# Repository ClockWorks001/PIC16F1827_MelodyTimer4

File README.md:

# PIC16F1827 Melody Timer Project.
---
This is a simple kitchen/cooking timer by [PIC16F1827][1].
It can choose which of 3 minutes, 5 minutes and 10 minutes.

## Description

This is a simple kitchen/cooking timer by [PIC16F1827][1].
It can choose which of 3 minutes, 5 minutes and 10 minutes.
When it became end of time, it sounds a melody.

I use following peripherals for this Melody Timer project.
  *TMR1* (with interrupt. It makes 1mil second interval.)
  *TMR2*
  *ECCP2*(with TMR2. I use it for PWM output. It buzz a piezo sounder.)
  *GPIO*(input x2 for Switches, output x3 for LED1, LED2, LED3)

Other references.
  <https://docs.google.com/spreadsheets/d/1fajrvUh0QQHbjQNBCf9UKNRYu8I2-zE32fsanEHT9bc/edit?usp=sharing>

## Demo

## Prerequisites

I created this project using the free versions of the following tools:
 * [Microchip MPLAB X][2] (v2.3)
 * [Microchip XC8 Compiler][3] (v1.32)
 * [MPLAB Code Configurator][4] (installed as plugin within MPLAB X)
 * [KICAD][6] (BZR4022)

You will need to download and install these tools appropriately before you
can open this project and build it.
I use the [Microchip MPLAB PICkit3 In-Circuit Debugger][5] to program
the chip and debug it.  

## Licence

[MIT](https://github.com/tcnksm/tool/blob/master/LICENCE)

## Author

Hiroshi Murakami  
<https://github.com/ClockWorks001>  

[1]: http://www.microchip.com/wwwproducts/Devices.aspx?dDocName=en538963 "PIC16F1827"
[2]: http://www.microchip.com/pagehandler/en-us/family/mplabx/ "MPLAB X"
[3]: http://www.microchip.com/pagehandler/en_us/devtools/mplabxc/ "MPLAB XC Compilers"
[4]: http://www.microchip.com/pagehandler/en-us/press-release/microchips-free-code-configura.html "MPLAB Code Configurator"
[5]: http://www.microchip.com/Developmenttools/ProductDetails.aspx?PartNO=PG164130 "MPLAB PICkit3 In-Circuit Debugger"
[6]: http://www.kicad-pcb.org/display/KICAD/KiCad+EDA+Software+Suite "KICAD"

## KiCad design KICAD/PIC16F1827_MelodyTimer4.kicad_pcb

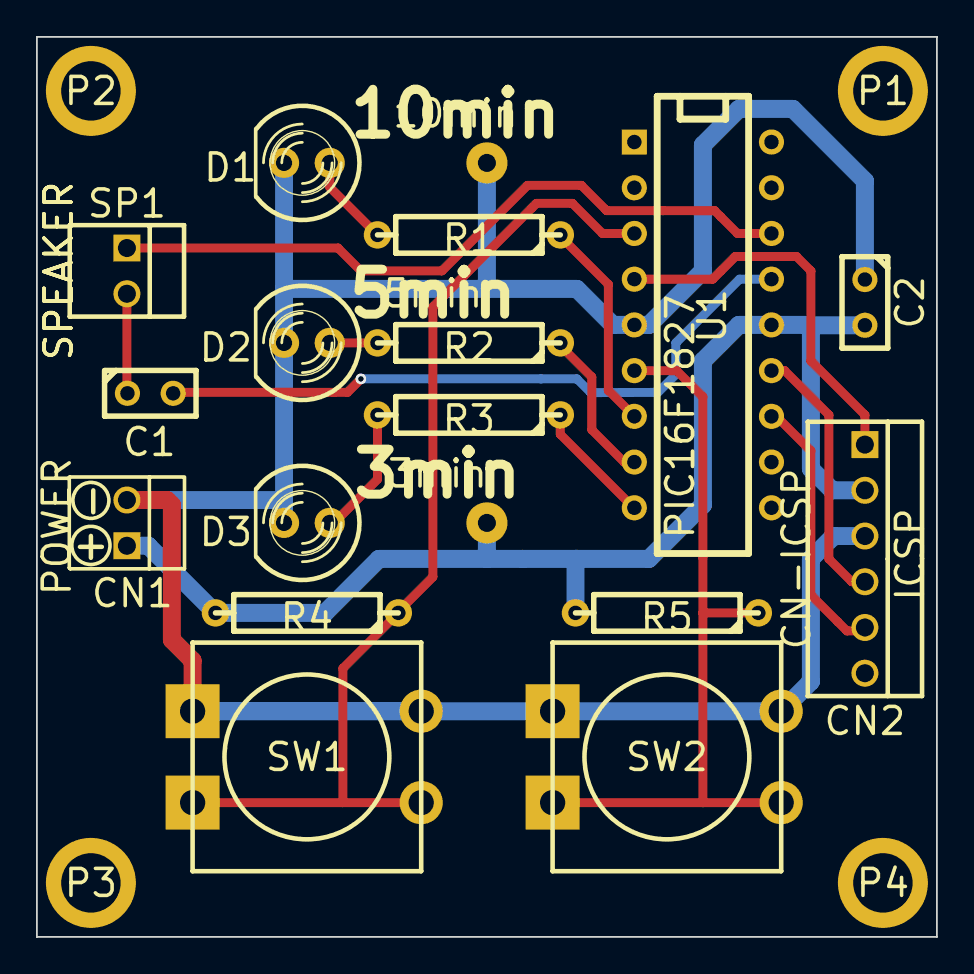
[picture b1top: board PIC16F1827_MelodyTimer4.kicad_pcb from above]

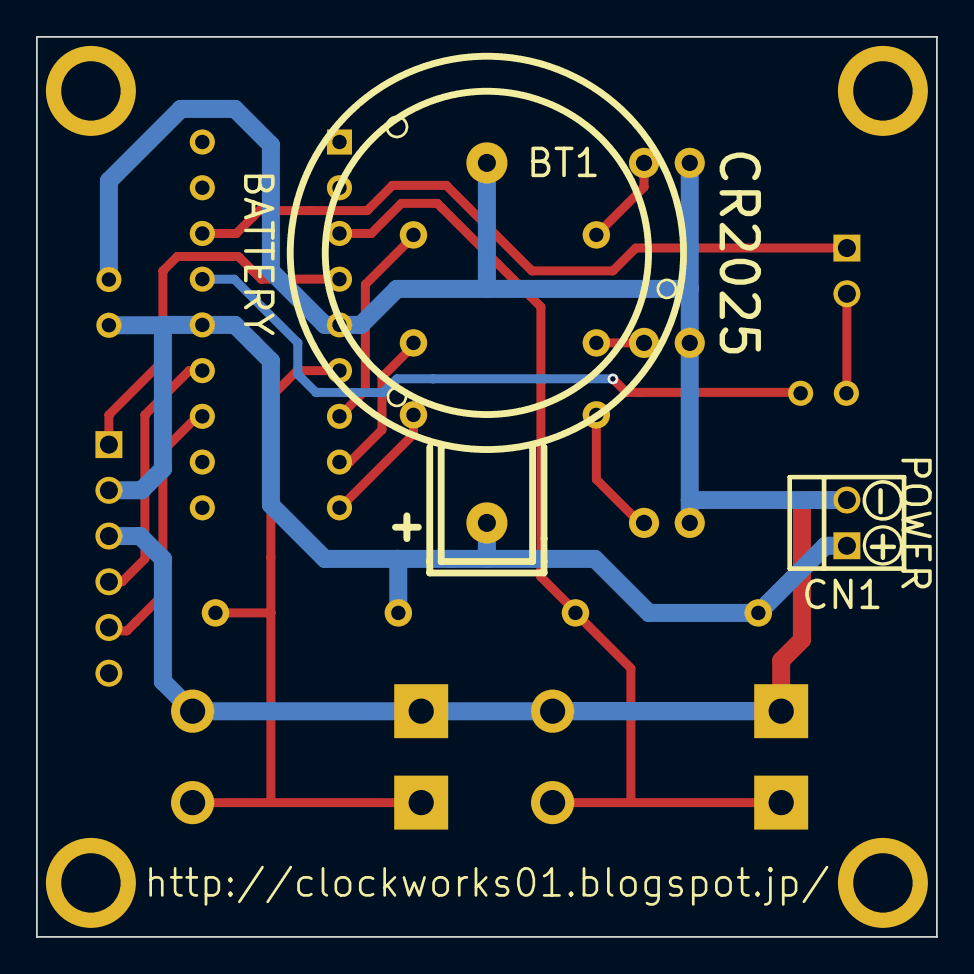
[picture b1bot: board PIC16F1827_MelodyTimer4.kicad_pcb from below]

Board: 2 copper layers, 50.0 x 50.0 mm, 21 parts (2 on the bottom side), 16 nets.

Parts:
BT1: BATTERY; CR2032H_AK
C1: 10uF; C1_MU
C2: 0.1uF; C1_MU
CN1: POWER; PINHEAD1-2_MU
CN2: CN-ICSP; PINHEAD1-6_MU
D1: 10min; LED-5MM_AK
D2: 5min; LED-5MM_AK
D3: 3min; LED-5MM_AK
P1, P2, P3, P4: PAD3mmX5mm
R1, R2, R3: 240; R4_MU
R4, R5: 10K; R4_MU
SP1: SPEAKER; PINHEAD1-2_MU
SW1, SW2: SW_PUSH-12mm_AK
U1: PIC16F1827; DIP-18__300_MU

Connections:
+3.3V: BT1.1, C2.2, CN1.1, CN2.2, R4.2, R5.2, U1.14
GND: BT1.2, C2.1, CN1.2, CN2.3, D1.2, D2.2, D3.2, SW1.1, SW2.1, U1.5
unnamed: C1.2, U1.15
unnamed: C1.1, SP1.2
unnamed: CN2.5, U1.12
unnamed: CN2.1, U1.4
unnamed: R3.1, U1.9
unnamed: R4.1, SW1.2, U1.3
unnamed: CN2.4, U1.13
unnamed: SP1.1, U1.16
unnamed: R1.1, U1.7
unnamed: D1.1, R1.2
unnamed: R2.1, U1.8
unnamed: D2.1, R2.2
unnamed: D3.1, R3.2
unnamed: R5.1, SW2.2, U1.6

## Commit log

2014-10-15 in mid compiling
2014-10-19 compail finished
2014-11-03 switch menu making
2015-02-15 compile up for cooking timer with 3,5,10min
2015-03-24 phase 1 programing done. pcb design done.
2015-03-24 phase 1 programing done. pcb design done.(2)
2015-03-24 phase 1 programing done. pcb design done.(3)
